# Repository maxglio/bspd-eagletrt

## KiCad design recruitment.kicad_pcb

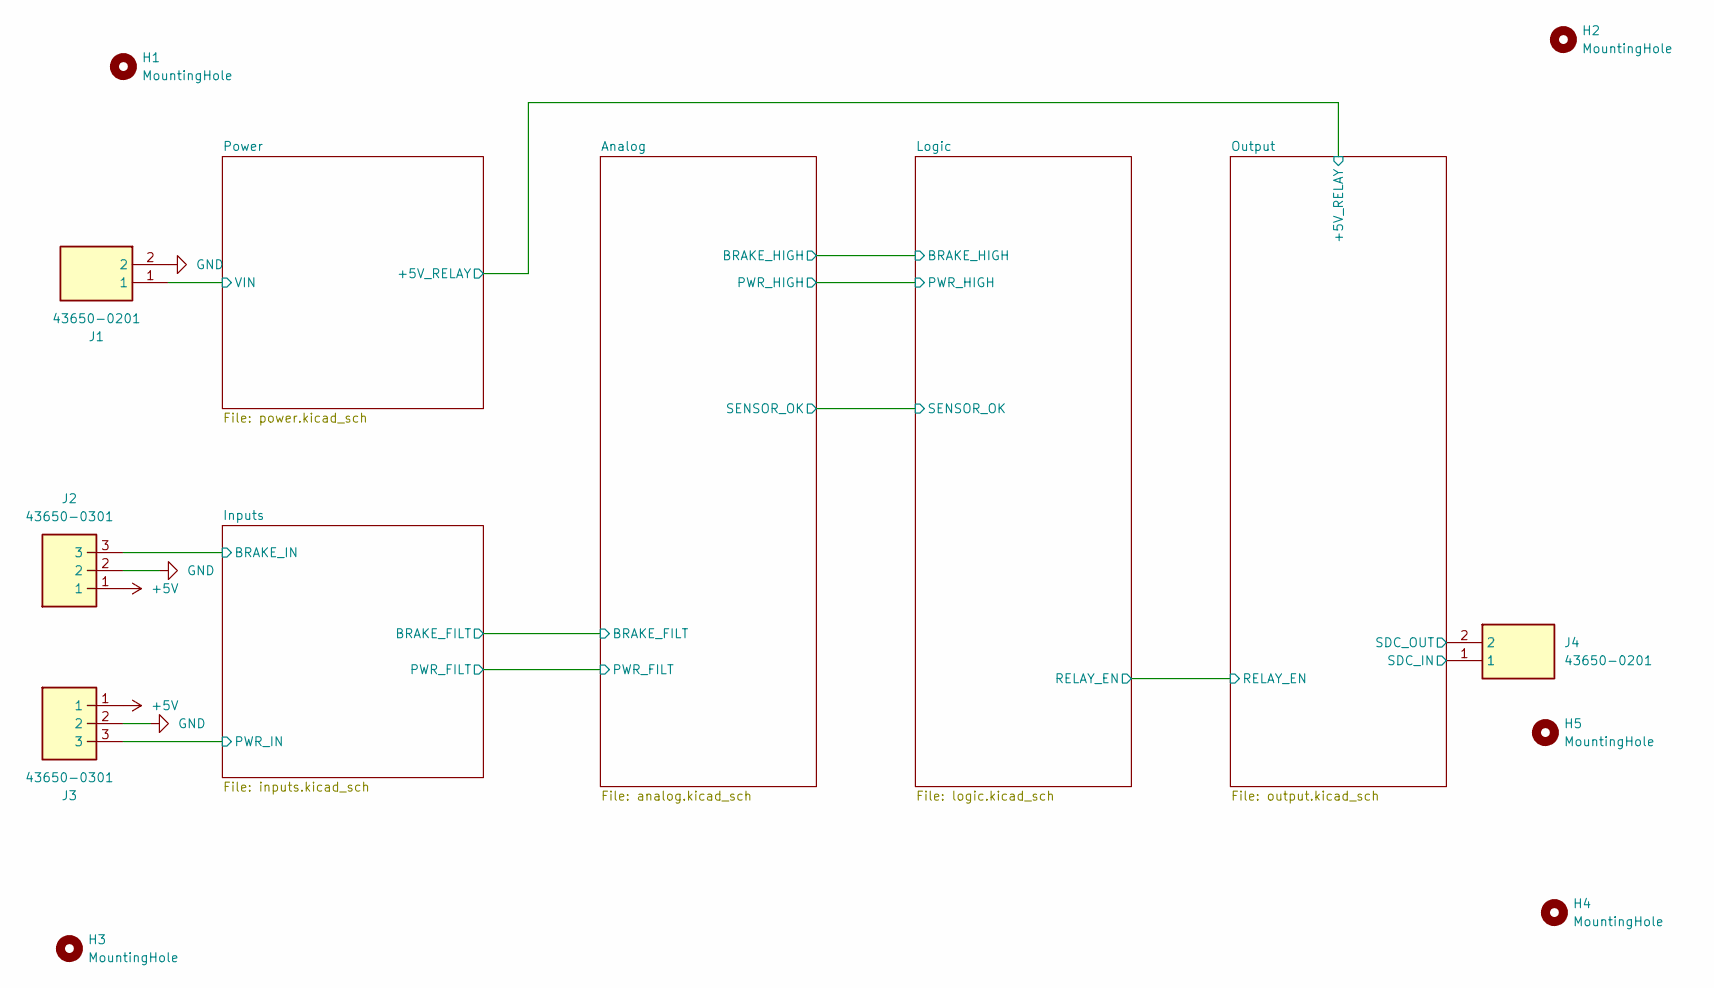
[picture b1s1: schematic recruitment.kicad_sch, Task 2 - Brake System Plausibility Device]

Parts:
H1, H2, H3, H4, H5: MountingHole; MountingHole_3.2mm_M3
J1, J4: 43650-0201; Molex_Micro-Fit_3.0_43045-0200_2x01_P3.00mm_Horizontal; Mouser Part Number 538-43650-0201
J2, J3: 43650-0301; 43650-03YY; Mouser Part Number 538-43650-0301

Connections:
+5V: J2.1, J3.1; also elsewhere on the board
/Inputs/BRAKE_IN: J2.3; also elsewhere on the board
/Inputs/PWR_IN: J3.3; also elsewhere on the board
/Output/SDC_IN: J4.1; also elsewhere on the board
/Output/SDC_OUT: J4.2; also elsewhere on the board
/Power/VIN: J1.1; also elsewhere on the board
GND: J1.2, J2.2, J3.2; also elsewhere on the board

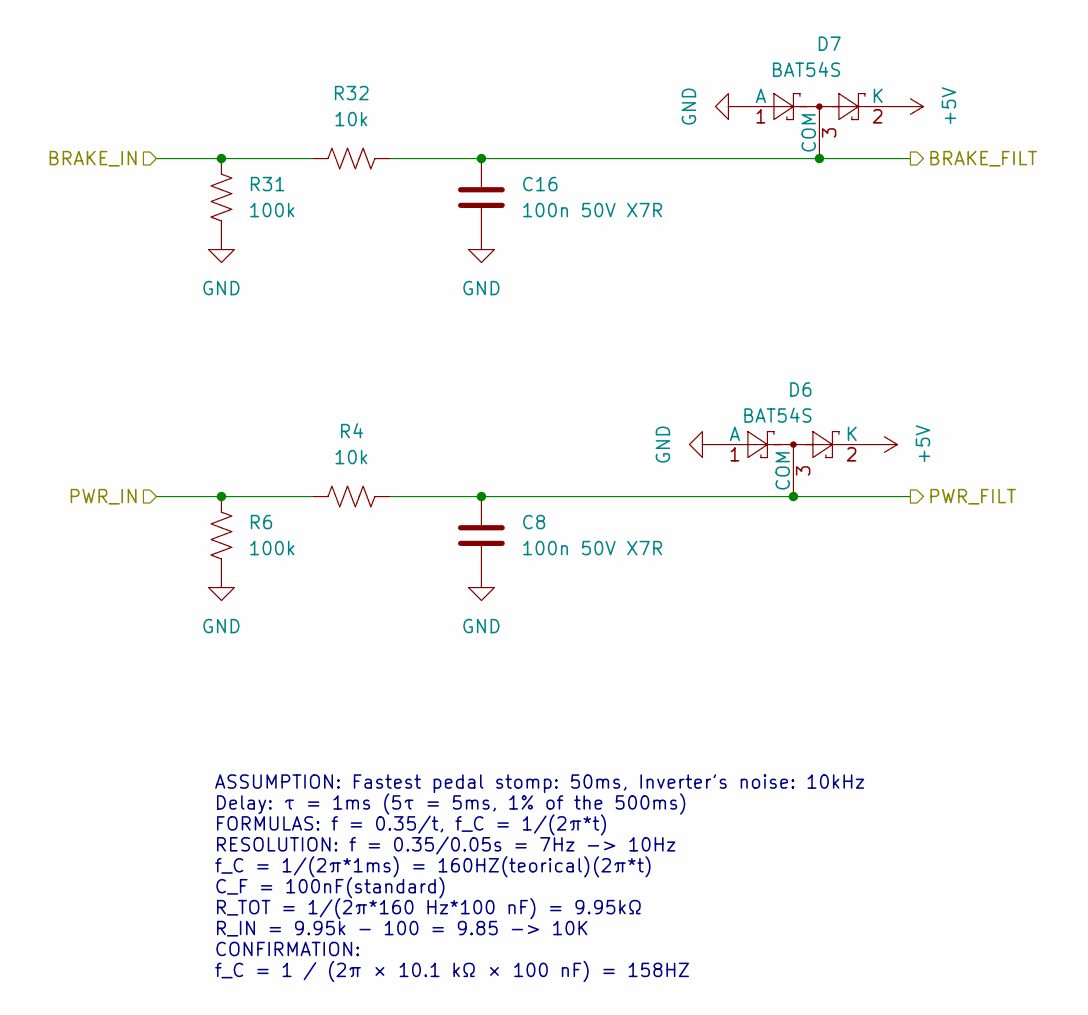
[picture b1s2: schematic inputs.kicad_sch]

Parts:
C8, C16: 100n 50V X7R; C_0603_1608Metric
D6, D7: BAT54S; SOT-23
R4, R32: 10k; R_0603_1608Metric
R6, R31: 100k; R_0603_1608Metric

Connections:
+5V: D6.2 (K), D7.2 (K); also elsewhere on the board
/Analog/BRAKE_FILT: C16.1, D7.3 (COM), R32.2; also elsewhere on the board
/Analog/PWR_FILT: C8.1, D6.3 (COM), R4.2; also elsewhere on the board
/Inputs/BRAKE_IN: R31.1, R32.1; also elsewhere on the board
/Inputs/PWR_IN: R4.1, R6.1; also elsewhere on the board
GND: C8.2, C16.2, D6.1 (A), D7.1 (A), R6.2, R31.2; also elsewhere on the board

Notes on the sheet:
ASSUMPTION: Fastest pedal stomp: 50ms, Inverter's noise: 10kHz Delay: τ = 1ms (5τ = 5ms, 1% of the 500ms) FORMULAS: f = 0.35/t, f_C = 1/(2π*t) RESOLUTION: f = 0.35/0.05s = 7Hz -> 10Hz f_C = 1/(2π*1ms) = 160HZ(teorical)(2π*t) C_F = 100nF(standard) R_TOT = 1/(2π*160 Hz*100 nF) = 9.95kΩ R_IN = 9.95k -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

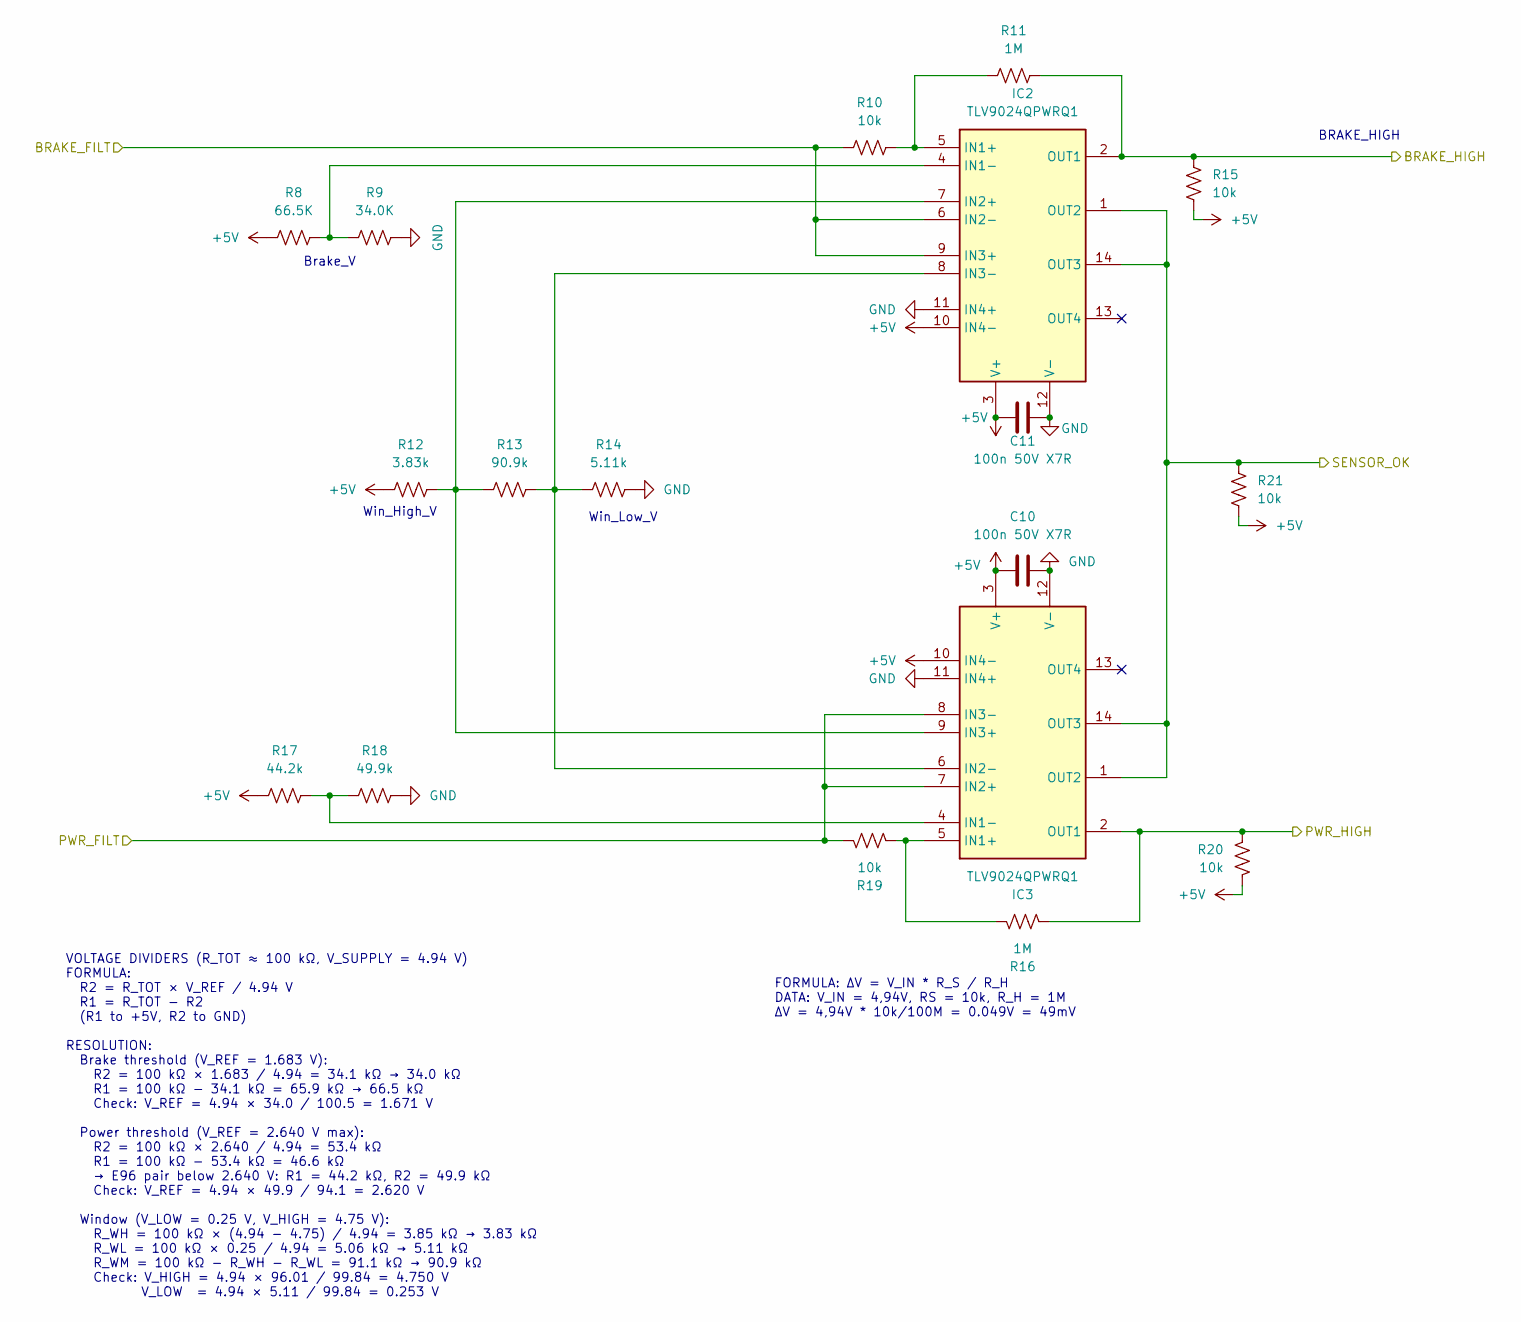
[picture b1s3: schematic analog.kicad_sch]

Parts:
C10, C11: 100n 50V X7R; C_0603_1608Metric
IC2, IC3: TLV9024QPWRQ1; SOP65P640X120-14N; Mouser Part Number 595-TLV9024QPWRQ1
R8: 66.5K; R_0603_1608Metric
R9: 34.0K; R_0603_1608Metric
R10, R15, R19, R20, R21: 10k; R_0603_1608Metric
R11, R16: 1M; R_0603_1608Metric
R12: 3.83k; R_0603_1608Metric
R13: 90.9k; R_0603_1608Metric
R14: 5.11k; R_0603_1608Metric
R17: 44.2k; R_0603_1608Metric
R18: 49.9k; R_0603_1608Metric

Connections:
+5V: C10.1, C11.1, IC2.3 (V+), IC2.10 (IN4-), IC3.3 (V+), IC3.10 (IN4-), R8.1, R12.1, R15.2, R17.1, R20.2, R21.2; also elsewhere on the board
/Analog/BRAKE_FILT: IC2.6 (IN2-), IC2.9 (IN3+), R10.1; also elsewhere on the board
/Analog/BRAKE_HIGH: IC2.2 (OUT1), R11.2, R15.1; also elsewhere on the board
/Analog/PWR_FILT: IC3.7 (IN2+), IC3.8 (IN3-), R19.1; also elsewhere on the board
/Analog/PWR_HIGH: IC3.2 (OUT1), R16.2, R20.1; also elsewhere on the board
/Analog/SENSOR_OK: IC2.1 (OUT2), IC2.14 (OUT3), IC3.1 (OUT2), IC3.14 (OUT3), R21.1; also elsewhere on the board
GND: C10.2, C11.2, IC2.11 (IN4+), IC2.12 (V-), IC3.11 (IN4+), IC3.12 (V-), R9.2, R14.2, R18.2; also elsewhere on the board
unnamed: IC2.5 (IN1+), R10.2, R11.1
unnamed: IC2.4 (IN1-), R8.2, R9.1
unnamed: IC2.7 (IN2+), IC3.9 (IN3+), R12.2, R13.1
unnamed: IC2.8 (IN3-), IC3.6 (IN2-), R13.2, R14.1
unnamed: IC3.5 (IN1+), R16.1, R19.2
unnamed: IC3.4 (IN1-), R17.2, R18.1

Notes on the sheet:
Brake_V
BRAKE_HIGH
Win_High_V
Win_Low_V
FORMULA: ΔV = V_IN * R_S / R_H DATA: V_IN = 4,94V, RS = 10k, R_H = 1M ΔV = 4,94V * 10k/100M = 0.049V = 49mV
VOLTAGE DIVIDERS (R_TOT ≈ 100 kΩ, V_SUPPLY = 4.94 V) FORMULA: R2 = R_TOT × V_REF / 4.94 V R1 = R_TOT − R2 (R1 to +5V, R2 to GND) RESOLUTION: Brake threshold (V_REF = 1.683 V): R2 = 100 kΩ × 1.683 / 4.94 = 34.1 kΩ → 34.0 kΩ R1 = 100 kΩ − 34.1 kΩ = 65.9 kΩ → 66.5 kΩ Check: V_REF = 4.94 × 34.0 / 100.5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

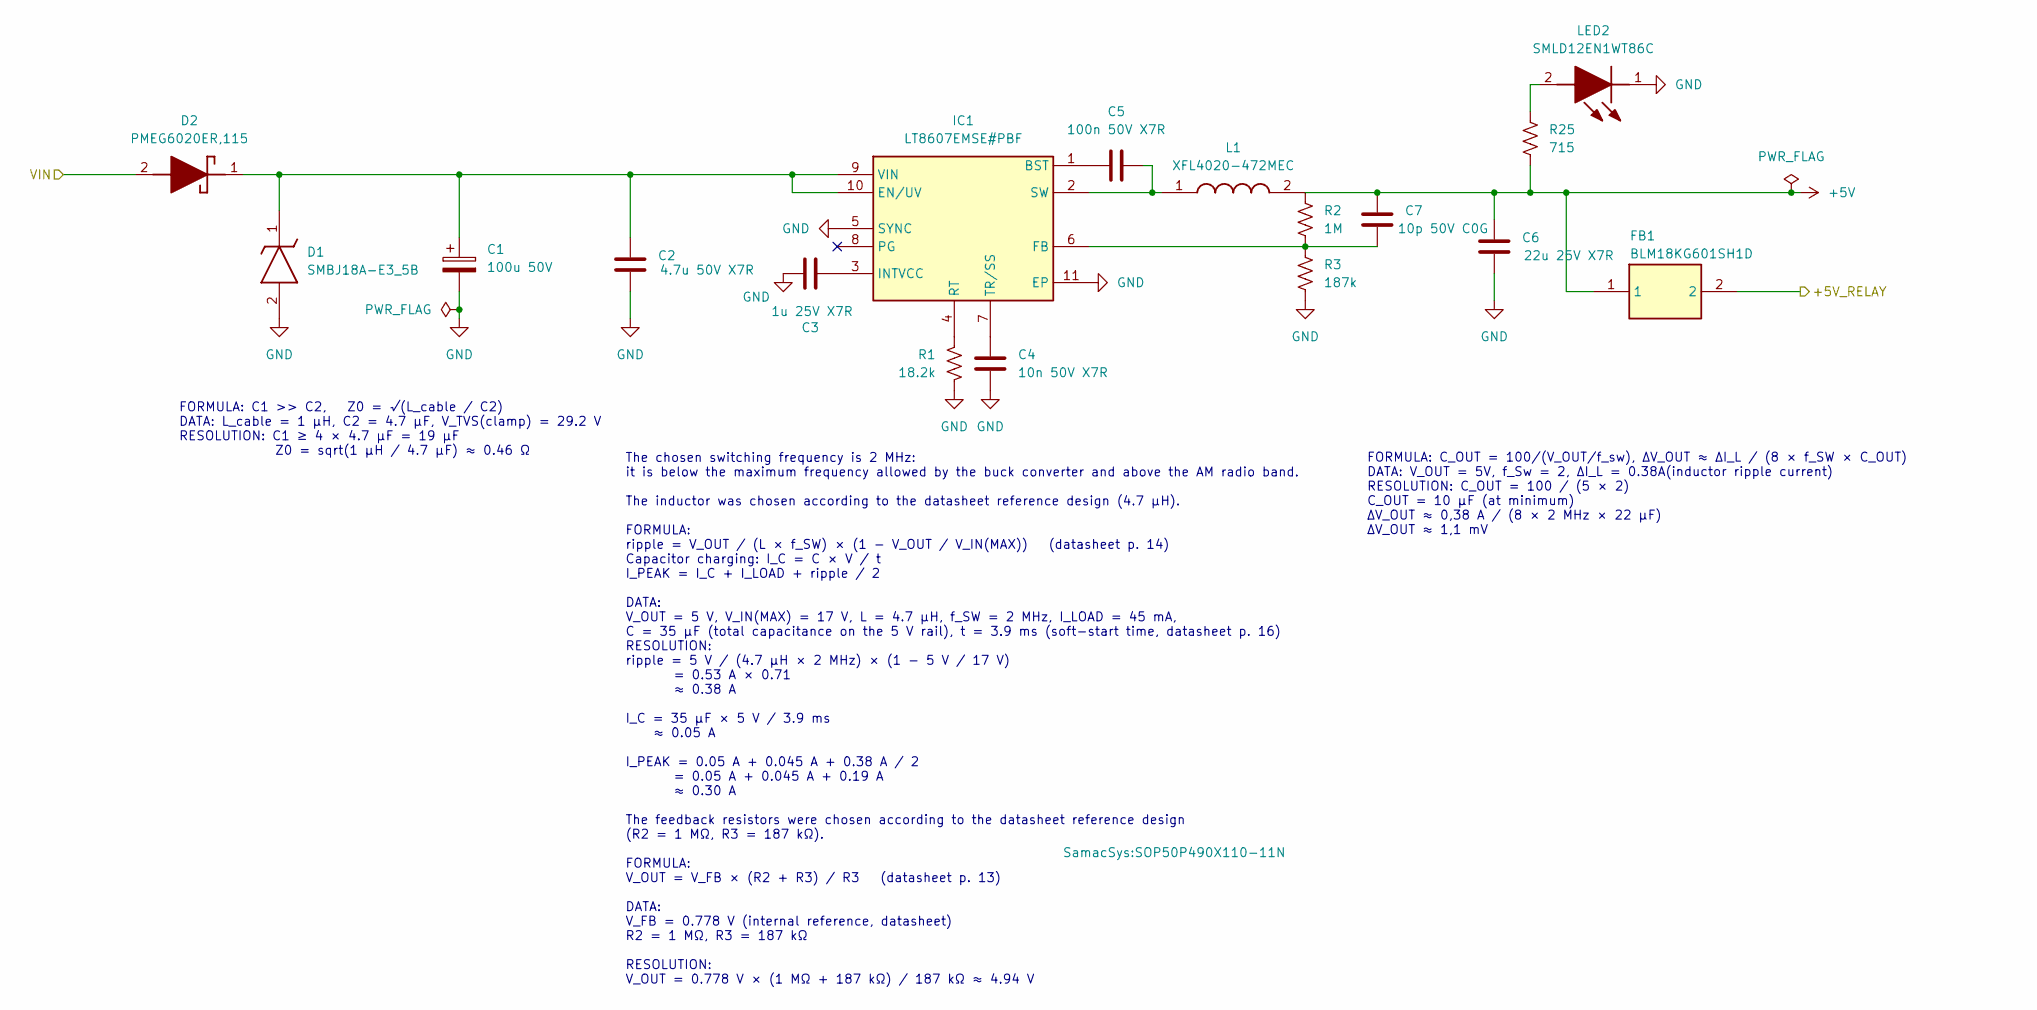
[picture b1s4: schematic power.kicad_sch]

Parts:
C1: 100u 50V; CP_Elec_8x10
C2: 4.7u 50V X7R; C_1206_3216Metric
C3: 1u 25V X7R; C_0603_1608Metric
C4: 10n 50V X7R; C_0603_1608Metric
C5: 100n 50V X7R; C_0603_1608Metric
C6: 22u 25V X7R; C_1210_3225Metric
C7: 10p 50V C0G; C_0603_1608Metric
D1: SMBJ18A-E3_5B; DIOM5436X244N; Mouser Part Number 625-SMBJ18A-E3/5B
D2: PMEG6020ER,115; PMEG6020ER115; Mouser Part Number 771-PMEG6020ER-115
FB1: BLM18KG601SH1D; BLM18SP221SN1B; Mouser Part Number 81-BLM18KG601SH1D
IC1: LT8607EMSE#PBF; SOP50P490X110-11N; Mouser Part Number 584-LT8607EMSE#PBF
L1: XFL4020-472MEC; XFL4020472MEC; Mouser Part Number 994-XFL4020-472MEC
LED2: SMLD12EN1WT86C; Mouser Part Number 755-SMLD12EN1WT86C
R1: 18.2k; R_0603_1608Metric
R2: 1M; R_0603_1608Metric
R3: 187k; R_0603_1608Metric
R25: 715; R_0603_1608Metric

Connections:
+5V: C6.1, C7.1, FB1.1, L1.2, R2.1, R25.2; also elsewhere on the board
/Output/+5V_RELAY: FB1.2; also elsewhere on the board
/Power/VIN: D2.2 (A); also elsewhere on the board
GND: C1.2, C2.2, C3.1, C4.2, C6.2, D1.2 (A), IC1.5 (SYNC), IC1.11 (EP), LED2.1 (K), R1.2, R3.2; also elsewhere on the board
unnamed: C1.1, C2.1, D1.1 (K), D2.1 (K), IC1.9 (VIN), IC1.10 (EN/UV)
unnamed: C5.1, IC1.1 (BST)
unnamed: C7.2, IC1.6 (FB), R2.2, R3.1
unnamed: C3.2, IC1.3 (INTVCC)
unnamed: IC1.4 (RT), R1.1
unnamed: C5.2, IC1.2 (SW), L1.1
unnamed: C4.1, IC1.7 (TR/SS)
unnamed: LED2.2 (A), R25.1

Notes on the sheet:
FORMULA: C_OUT = 100/(V_OUT/f_sw), ΔV_OUT ≈ ΔI_L / (8 × f_SW × C_OUT) DATA: V_OUT = 5V, f_Sw = 2, ΔI_L = 0.38A(inductor ripple current) RESOLUTION: C_OUT = 100 / (5 × 2) C_OUT = 10 µF (at minimum) ΔV_OUT ≈ 0,38 A / (8 × 2 MHz × 22 µF) ΔV_OUT ≈ 1,1 mV
FORMULA: C1 >> C2, Z0 = √(L_cable / C2) DATA: L_cable = 1 µH, C2 = 4.7 µF, V_TVS(clamp) = 29.2 V RESOLUTION: C1 ≥ 4 × 4.7 µF = 19 µF Z0 = sqrt(1 µH / 4.7 µF) ≈ 0.46 Ω
The chosen switching frequency is 2 MHz: it is below the maximum frequency allowed by the buck converter and above the AM radio band. The inductor was chosen according to the datasheet reference design (4.7 µH). FORMULA: ripple = V_OUT / (L × f_SW) × (1 − V_OUT / V_IN(MAX)) (datasheet p. 14) Capaci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

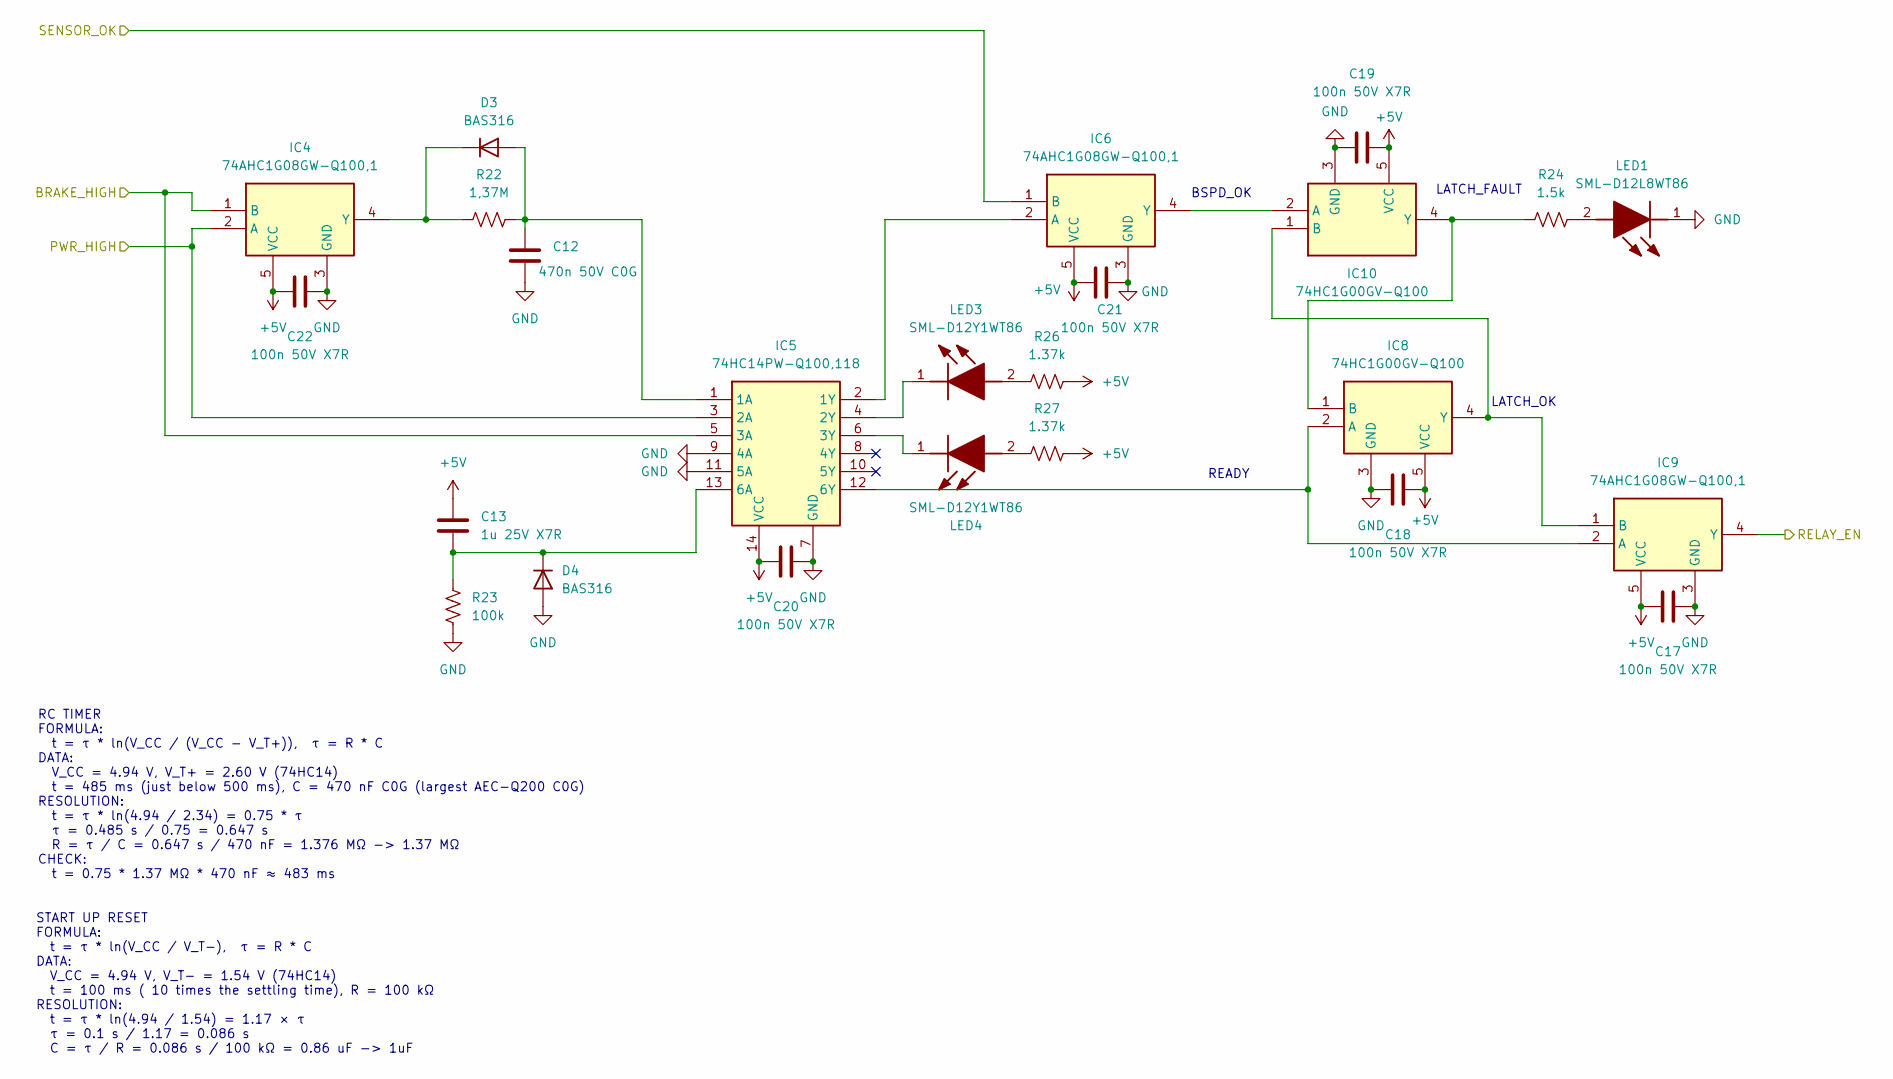
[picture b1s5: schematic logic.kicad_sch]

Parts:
C12: 470n 50V C0G; C_2220_5750Metric
C13: 1u 25V X7R; C_0603_1608Metric
C17, C18, C19, C20, C21, C22: 100n 50V X7R; C_0603_1608Metric
D3, D4: BAS316; D_SOD-323
IC4, IC6, IC9: 74AHC1G08GW-Q100,1; SOT65P212X110-5N; Mouser Part Number 771-74AHC1G08GW-Q100
IC5: 74HC14PW-Q100,118; SOP65P640X110-14N; Mouser Part Number 771-74HC14PW-Q100118
IC8, IC10: 74HC1G00GV-Q100; SOT95P275X110-5N; Mouser Part Number 771-74HC1G00GV
LED1: SML-D12L8WT86; SMLD12L8WT86; Mouser Part Number 755-SML-D12L8WT86
LED3, LED4: SML-D12Y1WT86; LEDC1608X55N; Mouser Part Number 755-SML-D12Y1WT86
R22: 1,37M; R_0603_1608Metric
R23: 100k; R_0603_1608Metric
R24: 1.5k; R_0603_1608Metric
R26, R27: 1.37k; R_0603_1608Metric

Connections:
+5V: C13.1, C17.1, C18.2, C19.2, C20.1, C21.1, C22.1, IC4.5 (VCC), IC5.14 (VCC), IC6.5 (VCC), IC8.5 (VCC), IC9.5 (VCC), IC10.5 (VCC), R26.2, R27.2; also elsewhere on the board
/Analog/BRAKE_HIGH: IC4.1 (B), IC5.5 (3A); also elsewhere on the board
/Analog/PWR_HIGH: IC4.2 (A), IC5.3 (2A); also elsewhere on the board
/Analog/SENSOR_OK: IC6.1 (B); also elsewhere on the board
/Logic/RELAY_EN: IC9.4 (Y); also elsewhere on the board
GND: C12.2, C17.2, C18.1, C19.1, C20.2, C21.2, C22.2, D4.2 (A), IC4.3 (GND), IC5.7 (GND), IC5.9 (4A), IC5.11 (5A), IC6.3 (GND), IC8.3 (GND), IC9.3 (GND), IC10.3 (GND), LED1.1 (K), R23.2; also elsewhere on the board
unnamed: C12.1, D3.2 (A), IC5.1 (1A), R22.2
unnamed: D3.1 (K), IC4.4 (Y), R22.1
unnamed: C13.2, D4.1 (K), IC5.13 (6A), R23.1
unnamed: IC5.2 (1Y), IC6.2 (A)
unnamed: IC5.4 (2Y), LED3.1 (K)
unnamed: IC5.6 (3Y), LED4.1 (K)
unnamed: IC5.12 (6Y), IC8.2 (A), IC9.2 (A)
unnamed: IC6.4 (Y), IC10.2 (A)
unnamed: IC8.4 (Y), IC9.1 (B), IC10.1 (B)
unnamed: IC8.1 (B), IC10.4 (Y), R24.1
unnamed: LED1.2 (A), R24.2
unnamed: LED3.2 (A), R26.1
unnamed: LED4.2 (A), R27.1

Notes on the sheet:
RC TIMER FORMULA: t = τ * ln(V_CC / (V_CC − V_T+)), τ = R * C DATA: V_CC = 4.94 V, V_T+ = 2.60 V (74HC14) t = 485 ms (just below 500 ms), C = 470 nF C0G (largest AEC-Q200 C0G) RESOLUTION: t = τ * ln(4.94 / 2.34) = 0.75 * τ τ = 0.485 s / 0.75 = 0.647 s R = τ / C = 0.647 s / 470 nF = 1.376 MΩ -> 1.37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
LATCH_OK
READY
START UP RESET FORMULA: t = τ * ln(V_CC / V_T−), τ = R * C DATA: V_CC = 4.94 V, V_T− = 1.54 V (74HC14) t = 100 ms ( 10 times the settling time), R = 100 kΩ RESOLUTION: t = τ * ln(4.94 / 1.54) = 1.17 × τ τ = 0.1 s / 1.17 = 0.086 s C = τ / R = 0.086 s / 100 kΩ = 0.86 uF -> 1uF
BSPD_OK
LATCH_FAULT

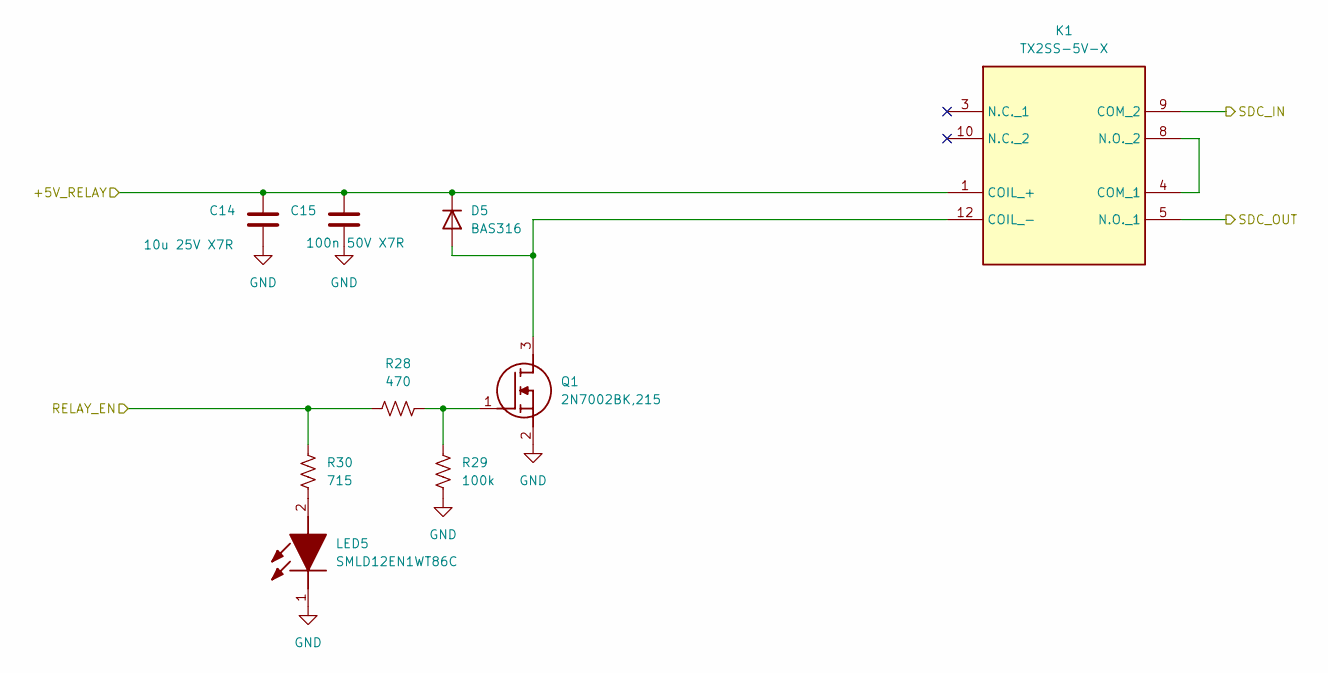
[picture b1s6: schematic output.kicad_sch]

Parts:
C14: 10u 25V X7R; C_1206_3216Metric
C15: 100n 50V X7R; C_0603_1608Metric
D5: BAS316; D_SOD-323
K1: TX2SS-5V-X; ATXS20020SS; Manufacturer_Part_Number TX2SS-5V-X
LED5: SMLD12EN1WT86C; Mouser Part Number 755-SMLD12EN1WT86C
Q1: 2N7002BK,215; SOT95P230X110-3N; Manufacturer_Part_Number 2N7002BK,215
R28: 470; R_0603_1608Metric
R29: 100k; R_0603_1608Metric
R30: 715; R_0603_1608Metric

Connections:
/Logic/RELAY_EN: R28.1, R30.1; also elsewhere on the board
/Output/+5V_RELAY: C14.2, C15.2, D5.1 (K), K1.1 (COIL_+); also elsewhere on the board
/Output/SDC_IN: K1.9 (COM_2); also elsewhere on the board
/Output/SDC_OUT: K1.5 (N.O._1); also elsewhere on the board
GND: C14.1, C15.1, LED5.1 (K), Q1.2 (S), R29.2; also elsewhere on the board
unnamed: D5.2 (A), K1.12 (COIL_-), Q1.3 (D)
unnamed: K1.4 (COM_1), K1.8 (N.O._2)
unnamed: LED5.2 (A), R30.2
unnamed: Q1.1 (G), R28.2, R29.1

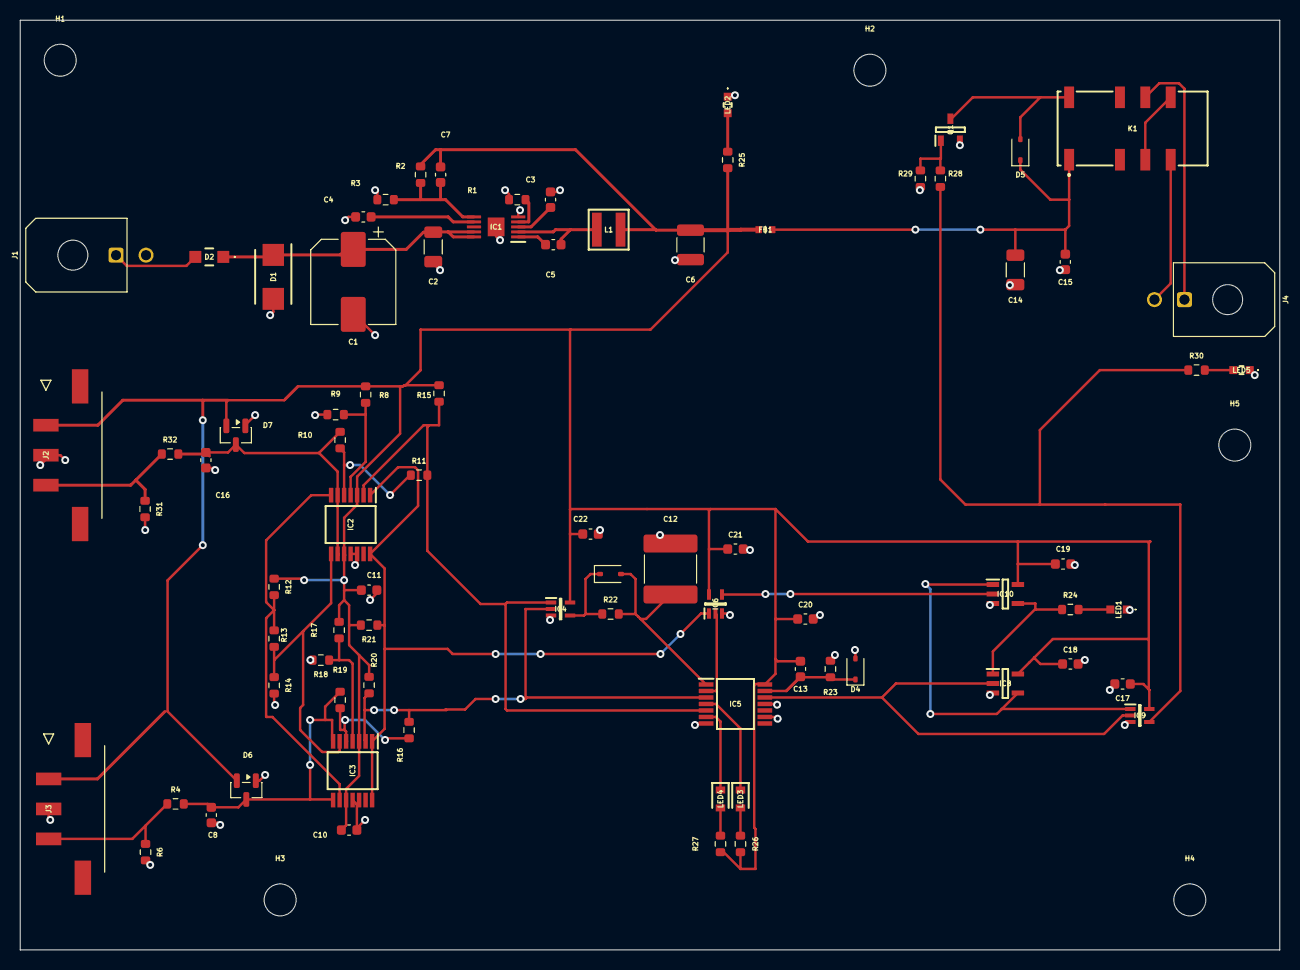
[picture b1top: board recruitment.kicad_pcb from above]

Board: 2 copper layers, 126.0 x 93.0 mm, 85 parts (0 on the bottom side), 45 nets.

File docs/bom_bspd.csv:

"Reference","Qty","Value","Manufacturer","MPN","Mouser","Footprint","Link","Note"
"C1","1","100u 50V","Panasonic","EEE-FK1H101P","667-EEE-FK1H101P","Capacitor_SMD:CP_Elec_8x10","https://www.mouser.it/ProductDetail/667-EEE-FK1H101P","Electrolytic, AEC-Q200"
"C2","1","4.7u 50V X7R","TDK","CGA5L3X7R1H475K160AB","810-CGA5L3X7R1H475KB","Capacitor_SMD:C_1206_3216Metric","https://www.mouser.it/ProductDetail/810-CGA5L3X7R1H475KB","AEC-Q200"
"C3,C13","2","1u 25V X7R","Murata","GCM188R71E105KA64D","81-GCM188R71E105KA4D","Capacitor_SMD:C_0603_1608Metric","https://www.mouser.it/ProductDetail/81-GCM188R71E105KA4D","AEC-Q200"
"C4","1","10n 50V X7R","Murata","GCM188R71H103KA37D","81-GCM188R71H103KA7D","Capacitor_SMD:C_0603_1608Metric","https://www.mouser.it/ProductDetail/81-GCM188R71H103KA7D","AEC-Q200"
"C5,C8,C10,C11,C15,C16,C17,C18,C19,C20,C21,C22","12","100n 50V X7R","Murata","GCM188R71H104KA57D","81-GCM188R71H104KA7D","Capacitor_SMD:C_0603_1608Metric","https://www.mouser.it/ProductDetail/81-GCM188R71H104KA7D","AEC-Q200"
"C6","1","22u 25V X7R","TDK","CGA6P3X7R1E226M250AE","810-CGA6P3X7R1E226M5","Capacitor_SMD:C_1210_3225Metric","https://www.mouser.it/ProductDetail/810-CGA6P3X7R1E226M5","AEC-Q200, soft termination"
"C7","1","10p 50V C0G","Murata","GCM1885C1H100JA16D","81-GCM1885C1H100JA6D","Capacitor_SMD:C_0603_1608Metric","https://www.mouser.it/ProductDetail/81-GCM1885C1H100JA6D","AEC-Q200"
"C12","1","470n 50V C0G","KEMET","C2220C474J5GACAUTO","80-C2220C474J5GAUTO","Capacitor_SMD:C_2220_5750Metric","https://www.mouser.it/ProductDetail/80-C2220C474J5GAUTO","AEC-Q200, timer capacitor"
"C14","1","10u 25V X7R","TDK","CGA5L1X7R1E106K160AE","810-CGA5L1X7R1E106KS","Capacitor_SMD:C_1206_3216Metric","https://www.mouser.it/ProductDetail/810-CGA5L1X7R1E106KS","AEC-Q200, soft termination"
"D1","1","SMBJ18A-E3/5B","Vishay","SMBJ18A-E3/5B","625-SMBJ18A-E3/5B","DIOM5436X244N","https://www.mouser.it/ProductDetail/625-SMBJ18A-E3%2F5B","TVS, 600 W"
"D2","1","PMEG6020ER,115","Nexperia","PMEG6020ER,115","771-PMEG6020ER-115","PMEG6020ER115","https://www.mouser.it/ProductDetail/771-PMEG6020ER-115","Schottky 60 V 2 A, AEC-Q101"
"D3,D4,D5","3","BAS316","Nexperia","BAS316,115","771-BAS316-T/R","Diode_SMD:D_SOD-323","https://www.mouser.it/ProductDetail/771-BAS316-T%2FR","AEC-Q101"
"D6,D7","2","BAT54S-Q","Nexperia","BAT54S-QR","771-BAT54S-QR","Package_TO_SOT_SMD:SOT-23","https://www.mouser.it/ProductDetail/771-BAT54S-QR","Dual series Schottky, AEC-Q101"
"FB1","1","BLM18KG601SH1D","Murata","BLM18KG601SH1D","81-BLM18KG601SH1D","Inductor_SMD:L_0603_1608Metric","https://www.mouser.it/ProductDetail/81-BLM18KG601SH1D","600 ohm at 100 MHz, 1.3 A, AEC-Q200"
"IC1","1","LT8607EMSE#WPBF","Analog Devices","LT8607EMSE#WPBF","584-LT8607EMSE#WPBF","SOP50P490X110-11N","https://www.mouser.it/ProductDetail/584-LT8607EMSE%23WPBF","Buck converter, AEC-Q100"
"IC2,IC3","2","TLV9024QPWRQ1","Texas Instruments","TLV9024QPWRQ1","595-TLV9024QPWRQ1","SOP65P640X120-14N","https://www.mouser.it/ProductDetail/595-TLV9024QPWRQ1","Quad comparator, AEC-Q100"
"IC4,IC6,IC9","3","74AHC1G08GW-Q100","Nexperia","74AHC1G08GW-Q100,1","771-74AHC1G08GW-Q100","SOT65P212X110-5N","https://www.mouser.it/ProductDetail/771-74AHC1G08GW-Q100","AND gate, AEC-Q100"
"IC5","1","74HC14PW-Q100","Nexperia","74HC14PW-Q100,118","771-74HC14PW-Q100118","SOP65P640X110-14N","https://www.mouser.it/ProductDetail/771-74HC14PW-Q100118","Hex Schmitt inverter, AEC-Q100"
"IC8,IC10","2","74HC1G00GV-Q100","Nexperia","74HC1G00GV-Q100H","771-74HC1G00GV-Q100H","SOT95P275X110-5N","https://www.mouser.it/ProductDetail/771-74HC1G00GV-Q100H","NAND gate, AEC-Q100"
"J1,J4","2","43650-0201","Molex","43650-0201","538-43650-0201","43650-02(00,01,02)","https://www.mouser.it/ProductDetail/538-43650-0201","Micro-Fit 3.0, 2 pins"
"J2,J3","2","43650-0301","Molex","43650-0301","538-43650-0301","43650-03YY","https://www.mouser.it/ProductDetail/538-43650-0301","Micro-Fit 3.0, 3 pins"
"K1","1","TX2SS-5V-X","Panasonic","TX2SS-5V-X","769-TX2SS-5V-X","ATXS20020SS","https://www.mouser.it/ProductDetail/769-TX2SS-5V-X","DPDT, 5 V coil, 2 A"
"L1","1","XFL4020-472MEC","Coilcraft","XFL4020-472MEC","994-XFL4020-472MEC","XFL4020472MEC","https://www.mouser.it/ProductDetail/994-XFL4020-472MEC","4.7 uH, AEC-Q200"
"LED1","1","SML-D12L8WT86","ROHM","SML-D12L8WT86","755-SML-D12L8WT86","SMLD12L8WT86","https://www.mouser.it/ProductDetail/755-SML-D12L8WT86","Red, AEC-Q102"
"LED2,LED5","2","SMLD12EN1WT86C","ROHM","SMLD12EN1WT86C","755-SMLD12EN1WT86C","SMLD12EN1WT86C","https://www.mouser.it/ProductDetail/755-SMLD12EN1WT86C","Green, AEC-Q102"
"LED3,LED4","2","SML-D12Y1WT86","ROHM","SML-D12Y1WT86","755-SML-D12Y1WT86","LEDC1608X55N","https://www.mouser.it/ProductDetail/755-SML-D12Y1WT86","Yellow, AEC-Q102"
"Q1","1","2N7002BK","Nexperia","2N7002BK,215","771-2N7002BK215","SOT95P230X110-3N","https://www.mouser.it/ProductDetail/771-2N7002BK215","N-MOSFET 60 V, AEC-Q101"
"R1","1","18.2k","Yageo","AC0603FR-0718K2L","603-AC0603FR-0718K2L","Resistor_SMD:R_0603_1608Metric","https://www.mouser.it/ProductDetail/603-AC0603FR-0718K2L","1 %, AEC-Q200"
"R2,R11,R16","3","1M","Yageo","AC0603FR-071ML","603-AC0603FR-071ML","Resistor_SMD:R_0603_1608Metric","https://www.mouser.it/ProductDetail/603-AC0603FR-071ML","1 %, AEC-Q200"
"R3","1","187k","Yageo","AC0603FR-07187KL","603-AC0603FR-07187KL","Resistor_SMD:R_0603_1608Metric","https://www.mouser.it/ProductDetail/603-AC0603FR-07187KL","1 %, AEC-Q200"
"R4,R10,R15,R19,R20,R21,R32","7","10k","Yageo","AC0603FR-0710KL","603-AC0603FR-0710KL","Resistor_SMD:R_0603_1608Metric","https://www.mouser.it/ProductDetail/603-AC0603FR-0710KL","1 %, AEC-Q200"
"R6,R23,R29,R31","4","100k","Yageo","AC0603FR-07100KL","603-AC0603FR-07100KL","Resistor_SMD:R_0603_1608Metric","https://www.mouser.it/ProductDetail/603-AC0603FR-07100KL","1 %, AEC-Q200"
"R8","1","66.5k","Yageo","AC0603FR-0766K5L","603-AC0603FR-0766K5L","Resistor_SMD:R_0603_1608Metric","https://www.mouser.it/ProductDetail/603-AC0603FR-0766K5L","1 %, AEC-Q200"
"R9","1","34.0k","Yageo","AC0603FR-0734KL","603-AC0603FR-0734KL","Resistor_SMD:R_0603_1608Metric","https://www.mouser.it/ProductDetail/603-AC0603FR-0734KL","1 %, AEC-Q200"
"R12","1","3.83k","Yageo","AC0603FR-073K83L","603-AC0603FR-073K83L","Resistor_SMD:R_0603_1608Metric","https://www.mouser.it/ProductDetail/603-AC0603FR-073K83L","1 %, AEC-Q200"
"R13","1","90.9k","Yageo","AC0603FR-0790K9L","603-AC0603FR-0790K9L","Resistor_SMD:R_0603_1608Metric","https://www.mouser.it/ProductDetail/603-AC0603FR-0790K9L","1 %, AEC-Q200"
"R14","1","5.11k","Yageo","AC0603FR-075K11L","603-AC0603FR-075K11L","Resistor_SMD:R_0603_1608Metric","https://www.mouser.it/ProductDetail/603-AC0603FR-075K11L","1 %, AEC-Q200"
"R17","1","44.2k","Yageo","AC0603FR-0744K2L","603-AC0603FR-0744K2L","Resistor_SMD:R_0603_1608Metric","https://www.mouser.it/ProductDetail/603-AC0603FR-0744K2L","1 %, AEC-Q200"
"R18","1","49.9k","Yageo","AC0603FR-0749K9L","603-AC0603FR-0749K9L","Resistor_SMD:R_0603_1608Metric","https://www.mouser.it/ProductDetail/603-AC0603FR-0749K9L","1 %, AEC-Q200"
"R22","1","1.37M","Yageo","AC0603FR-071M37L","603-AC0603FR-071M37L","Resistor_SMD:R_0603_1608Metric","https://www.mouser.it/ProductDetail/603-AC0603FR-071M37L","1 %, AEC-Q200, timer resistor"
"R24","1","1.5k","Yageo","AC0603FR-071K5L","603-AC0603FR-071K5L","Resistor_SMD:R_0603_1608Metric","https://www.mouser.it/ProductDetail/603-AC0603FR-071K5L","1 %, AEC-Q200"
"R25,R30","2","715","Yageo","AC0603FR-07715RL","603-AC0603FR-07715RL","Resistor_SMD:R_0603_1608Metric","https://www.mouser.it/ProductDetail/603-AC0603FR-07715RL","1 %, AEC-Q200"
"R26,R27","2","1.37k","Yageo","AC0603FR-071K37L","603-AC0603FR-071K37L","Resistor_SMD:R_0603_1608Metric","https://www.mouser.it/ProductDetail/603-AC0603FR-071K37L","1 %, AEC-Q200"
"R28","1","470","Yageo","AC0603FR-07470RL","603-AC0603FR-07470RL","Resistor_SMD:R_0603_1608Metric","https://www.mouser.it/ProductDetail/603-AC0603FR-07470RL","1 %, AEC-Q200"
